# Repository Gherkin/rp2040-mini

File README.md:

# A small MCU board using rp2040

ibom: https://gherkin.github.io/rp2040-mini/

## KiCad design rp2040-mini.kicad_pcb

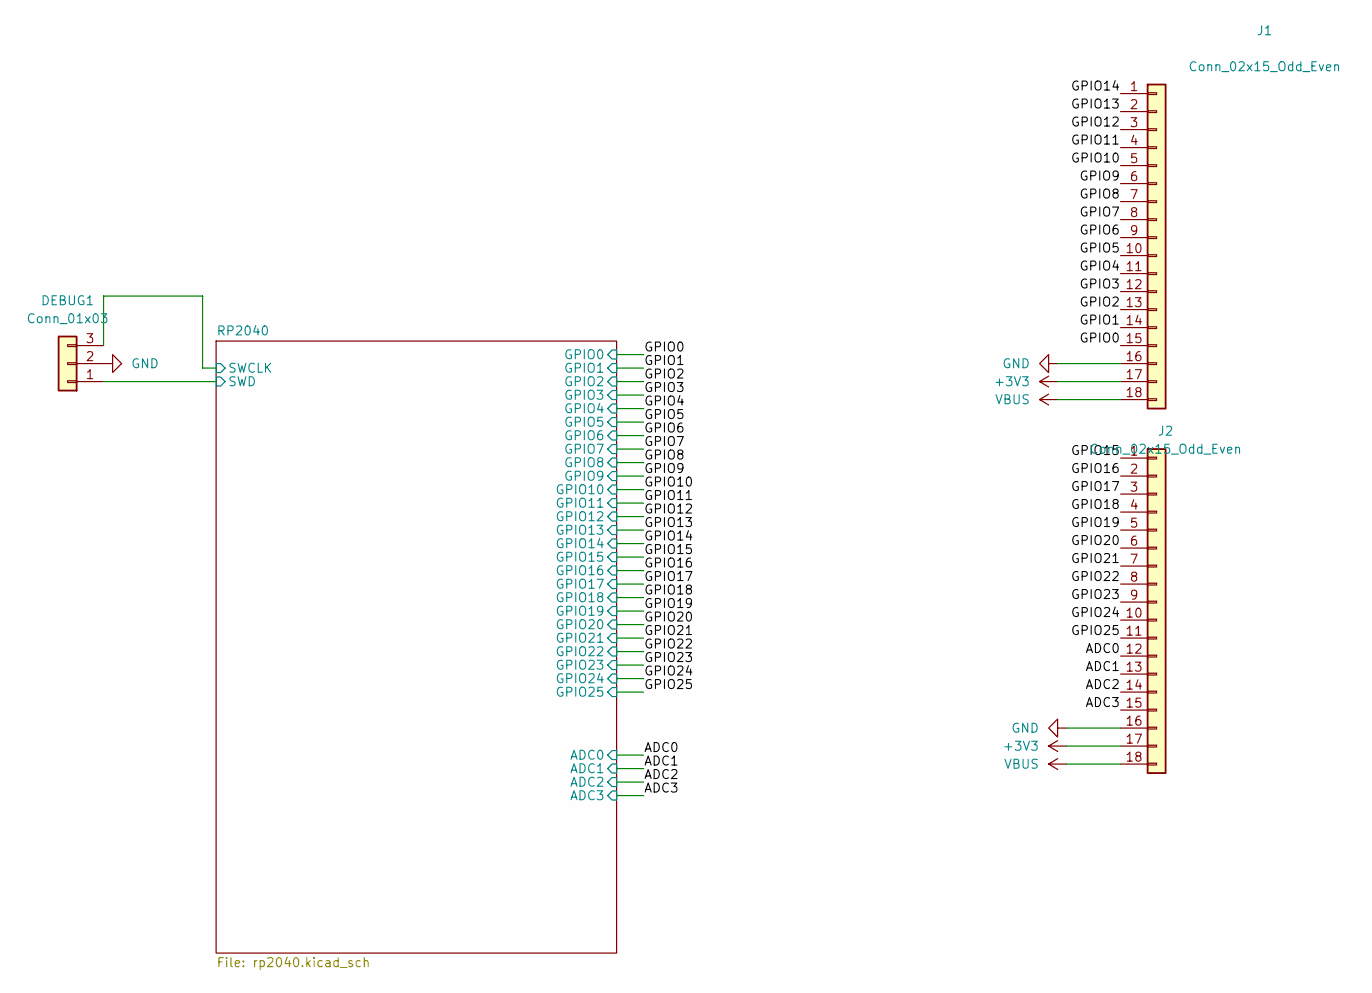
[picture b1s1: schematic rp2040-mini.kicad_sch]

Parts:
DEBUG1: Conn_01x03; PinHeader_1x03_P2.54mm_Vertical
J1, J2: Conn_02x15_Odd_Even; PinSocket_1x18_P2.54mm_Vertical

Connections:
+3V3: J1.17, J2.17; also elsewhere on the board
/ADC0: J2.12; also elsewhere on the board
/ADC1: J2.13; also elsewhere on the board
/ADC2: J2.14; also elsewhere on the board
/ADC3: J2.15; also elsewhere on the board
/GPIO0: J1.15; also elsewhere on the board
/GPIO1: J1.14; also elsewhere on the board
/GPIO2: J1.13; also elsewhere on the board
/GPIO3: J1.12; also elsewhere on the board
/GPIO4: J1.11; also elsewhere on the board
/GPIO5: J1.10; also elsewhere on the board
/GPIO6: J1.9; also elsewhere on the board
/GPIO7: J1.8; also elsewhere on the board
/GPIO8: J1.7; also elsewhere on the board
/GPIO9: J1.6; also elsewhere on the board
/GPIO10: J1.5; also elsewhere on the board
/GPIO11: J1.4; also elsewhere on the board
/GPIO12: J1.3; also elsewhere on the board
/GPIO13: J1.2; also elsewhere on the board
/GPIO14: J1.1; also elsewhere on the board
/GPIO15: J2.1; also elsewhere on the board
/GPIO16: J2.2; also elsewhere on the board
/GPIO17: J2.3; also elsewhere on the board
/GPIO18: J2.4; also elsewhere on the board
/GPIO19: J2.5; also elsewhere on the board
/GPIO20: J2.6; also elsewhere on the board
/GPIO21: J2.7; also elsewhere on the board
/GPIO22: J2.8; also elsewhere on the board
/GPIO23: J2.9; also elsewhere on the board
/GPIO24: J2.10; also elsewhere on the board
/GPIO25: J2.11; also elsewhere on the board
GND: DEBUG1.2, J1.16, J2.16; also elsewhere on the board
VBUS: J1.18, J2.18; also elsewhere on the board

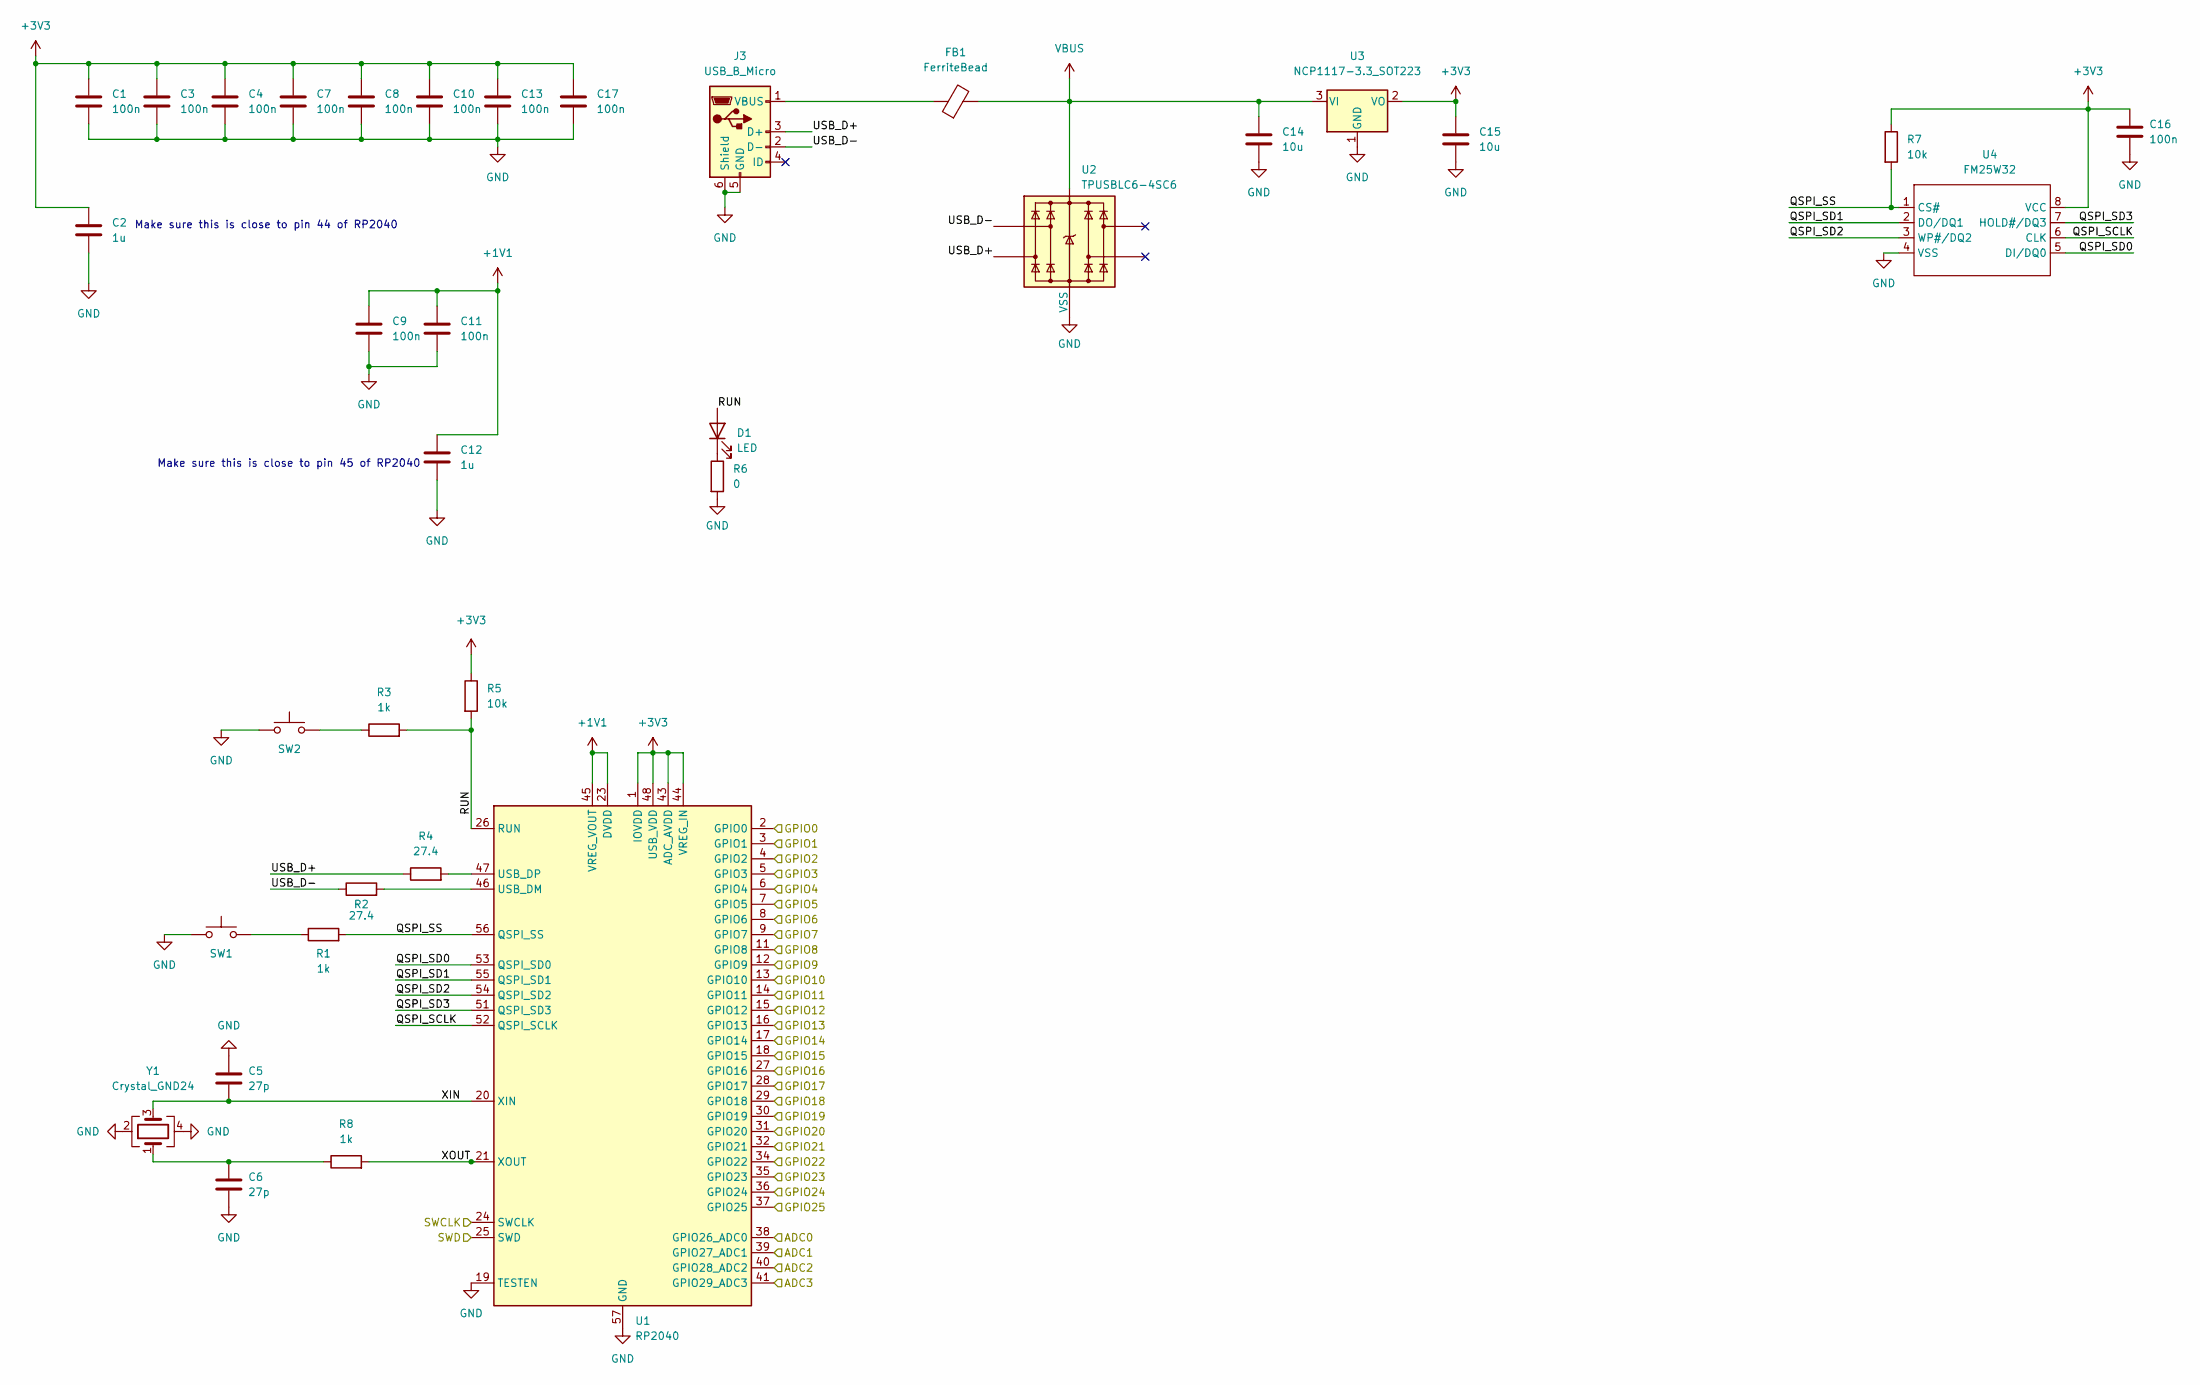
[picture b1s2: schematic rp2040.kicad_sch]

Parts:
C1, C3, C4, C7, C8, C9, C10, C11, C13, C16, C17: 100n; C_0402_1005Metric_Pad0.74x0.62mm_HandSolder; LCSC C60474
C2, C12: 1u; C_0402_1005Metric_Pad0.74x0.62mm_HandSolder; LCSC C59782
C5, C6: 27p; C_0402_1005Metric_Pad0.74x0.62mm_HandSolder; LCSC C107002
C14, C15: 10u; C_0402_1005Metric_Pad0.74x0.62mm_HandSolder; LCSC C85713
D1: LED; LED_0603_1608Metric_Pad1.05x0.95mm_HandSolder; LCSC C965804
FB1: FerriteBead; R_0402_1005Metric_Pad0.72x0.64mm_HandSolder; LCSC C85813
J3: USB_B_Micro; DEALON USB-MR-D-037; LCSC C2927008
R1, R3, R8: 1k; R_0402_1005Metric_Pad0.72x0.64mm_HandSolder; LCSC C114949
R2, R4: 27.4; R_0402_1005Metric_Pad0.72x0.64mm_HandSolder; LCSC C226391
R5, R7: 10k; R_0402_1005Metric_Pad0.72x0.64mm_HandSolder; LCSC C60490
R6: 0; R_0402_1005Metric_Pad0.72x0.64mm_HandSolder; LCSC C60485
SW1, SW2: SW_Push; BZCN TSC003A0826A; LCSC C2888477
U1: RP2040; QFN-56-1EP_7x7mm_P0.4mm_EP3.2x3.2mm; LCSC C2040
U2: TPUSBLC6-4SC6; SOT-23-6_Handsoldering; LCSC C558419
U3: NCP1117-3.3_SOT223; SOT-223-3_TabPin2; LCSC C26537
U4: FM25W32; SOP-8_5.28x5.23mm_P1.27mm; LCSC C609616
Y1: Crystal_GND24; Crystal_SMD_3225-4Pin_3.2x2.5mm; LCSC C9002

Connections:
+1V1: C9.1, C11.1, C12.1, U1.23 (DVDD), U1.45 (VREG_VOUT), U1.50 (DVDD)
+3V3: C1.1, C2.1, C3.1, C4.1, C7.1, C8.1, C10.1, C13.1, C15.1, C16.1, C17.1, R5.1, R7.1, U1.1 (IOVDD), U1.10 (IOVDD), U1.22 (IOVDD), U1.33 (IOVDD), U1.42 (IOVDD), U1.43 (ADC_AVDD), U1.44 (VREG_IN), U1.48 (USB_VDD), U1.49 (IOVDD), U3.2 (VO), U4.8 (VCC); also elsewhere on the board
/ADC0: U1.38 (GPIO26_ADC0); also elsewhere on the board
/ADC1: U1.39 (GPIO27_ADC1); also elsewhere on the board
/ADC2: U1.40 (GPIO28_ADC2); also elsewhere on the board
/ADC3: U1.41 (GPIO29_ADC3); also elsewhere on the board
/GPIO0: U1.2 (GPIO0); also elsewhere on the board
/GPIO1: U1.3 (GPIO1); also elsewhere on the board
/GPIO2: U1.4 (GPIO2); also elsewhere on the board
/GPIO3: U1.5 (GPIO3); also elsewhere on the board
/GPIO4: U1.6 (GPIO4); also elsewhere on the board
/GPIO5: U1.7 (GPIO5); also elsewhere on the board
/GPIO6: U1.8 (GPIO6); also elsewhere on the board
/GPIO7: U1.9 (GPIO7); also elsewhere on the board
/GPIO8: U1.11 (GPIO8); also elsewhere on the board
/GPIO9: U1.12 (GPIO9); also elsewhere on the board
/GPIO10: U1.13 (GPIO10); also elsewhere on the board
/GPIO11: U1.14 (GPIO11); also elsewhere on the board
/GPIO12: U1.15 (GPIO12); also elsewhere on the board
/GPIO13: U1.16 (GPIO13); also elsewhere on the board
/GPIO14: U1.17 (GPIO14); also elsewhere on the board
/GPIO15: U1.18 (GPIO15); also elsewhere on the board
/GPIO16: U1.27 (GPIO16); also elsewhere on the board
/GPIO17: U1.28 (GPIO17); also elsewhere on the board
/GPIO18: U1.29 (GPIO18); also elsewhere on the board
/GPIO19: U1.30 (GPIO19); also elsewhere on the board
/GPIO20: U1.31 (GPIO20); also elsewhere on the board
/GPIO21: U1.32 (GPIO21); also elsewhere on the board
/GPIO22: U1.34 (GPIO22); also elsewhere on the board
/GPIO23: U1.35 (GPIO23); also elsewhere on the board
/GPIO24: U1.36 (GPIO24); also elsewhere on the board
/GPIO25: U1.37 (GPIO25); also elsewhere on the board
/RP2040/QSPI_SCLK: U1.52 (QSPI_SCLK), U4.6 (CLK)
/RP2040/QSPI_SD0: U1.53 (QSPI_SD0), U4.5 (DI/DQ0)
/RP2040/QSPI_SD1: U1.55 (QSPI_SD1), U4.2 (DO/DQ1)
/RP2040/QSPI_SD2: U1.54 (QSPI_SD2), U4.3 (WP#/DQ2)
/RP2040/QSPI_SD3: U1.51 (QSPI_SD3), U4.7 (HOLD#/DQ3)
/RP2040/QSPI_SS: R1.2, R7.2, U1.56 (QSPI_SS), U4.1 (CS#)
/RP2040/RUN: D1.2 (A), R3.2, R5.2, U1.26 (RUN)
/RP2040/SWCLK: U1.24 (SWCLK); also elsewhere on the board
/RP2040/SWD: U1.25 (SWD); also elsewhere on the board
/RP2040/USB_D+: J3.3 (D+), R4.1, U2.1
/RP2040/USB_D-: J3.2 (D-), R2.1, U2.6
/RP2040/XIN: C5.2, U1.20 (XIN), Y1.3
/RP2040/XOUT: R8.2, U1.21 (XOUT)
GND: C1.2, C2.2, C3.2, C4.2, C5.1, C6.2, C7.2, C8.2, C9.2, C10.2, C11.2, C12.2, C13.2, C14.2, C15.2, C16.2, C17.2, J3.5 (GND), J3.6 (Shield), R6.2, SW1.1, SW2.1, U1.19 (TESTEN), U1.57 (GND), U2.2 (VSS), U3.1 (GND), U4.4 (VSS), Y1.2, Y1.4; also elsewhere on the board
unnamed: C6.1, R8.1, Y1.1
unnamed: D1.1 (K), R6.1
unnamed: FB1.1, J3.1 (VBUS)
unnamed: R1.1, SW1.2
unnamed: R2.2, U1.46 (USB_DM)
unnamed: R3.1, SW2.2
unnamed: R4.2, U1.47 (USB_DP)
VBUS: C14.1, FB1.2, U2.5, U3.3 (VI); also elsewhere on the board

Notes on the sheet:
Make sure this is close to pin 45 of RP2040
Make sure this is close to pin 44 of RP2040

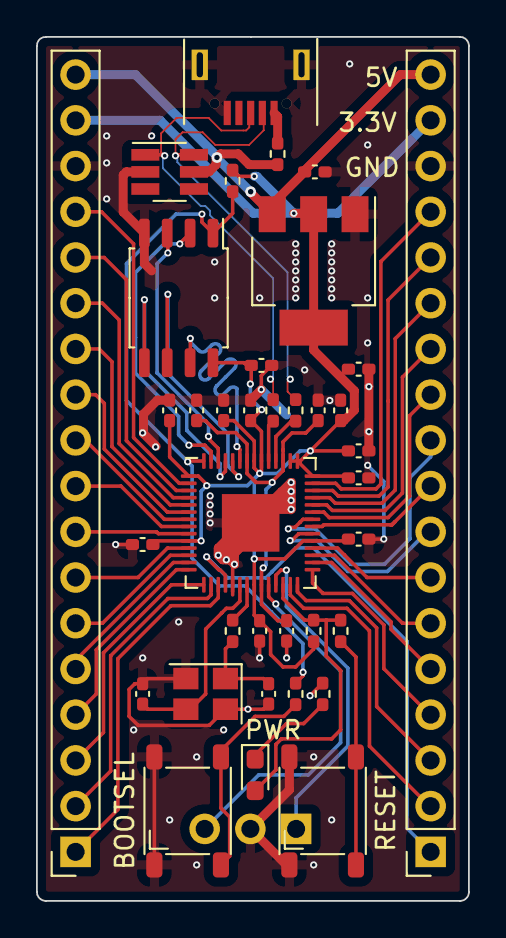
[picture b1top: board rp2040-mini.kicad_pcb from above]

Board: 4 copper layers, 24.0 x 48.0 mm, 38 parts (1 on the bottom side), 54 nets.

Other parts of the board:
DEBUG: Conn_01x03; PinHeader_1x03_P2.54mm_Vertical

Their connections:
/RP2040/SWCLK: DEBUG.3; also elsewhere on the board
/RP2040/SWD: DEBUG.1; also elsewhere on the board
GND: DEBUG.2; also elsewhere on the board

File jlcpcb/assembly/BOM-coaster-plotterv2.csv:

Comment,Designator,Footprint,LCSC
27p,"C5,C6",C_0402_1005Metric_Pad0.74x0.62mm_HandSolder,C107002
1k,"R1,R3,R8",R_0402_1005Metric_Pad0.72x0.64mm_HandSolder,C114949
RP2040,U1,QFN-56-1EP_7x7mm_P0.4mm_EP3.2x3.2mm,C2040
27.4,"R2,R4",R_0402_1005Metric_Pad0.72x0.64mm_HandSolder,C226391
NCP1117-3.3_SOT223,U3,SOT-223-3_TabPin2,C26537
SW_Push,"SW1,SW2",BZCN TSC003A0826A,C2888477
USB_B_Micro,J3,DEALON USB-MR-D-037,C2927008
TPUSBLC6-4SC6,U2,SOT-23-6_Handsoldering,C558419
1u,"C12,C2",C_0402_1005Metric_Pad0.74x0.62mm_HandSolder,C59782
100n,"C1,C10,C11,C13,C16,C17,C3,C4,C7,C8,C9",C_0402_1005Metric_Pad0.74x0.62mm_HandSolder,C60474
R,R6,R_0402_1005Metric_Pad0.72x0.64mm_HandSolder,C60485
10k,"R5,R7",R_0402_1005Metric_Pad0.72x0.64mm_HandSolder,C60490
FM25W32,U4,SOP-8_5.28x5.23mm_P1.27mm,C609616
10u,"C14,C15",C_0402_1005Metric_Pad0.74x0.62mm_HandSolder,C85713
FerriteBead,FB1,R_0402_1005Metric_Pad0.72x0.64mm_HandSolder,C85813
Crystal_GND24,Y1,Crystal_SMD_3225-4Pin_3.2x2.5mm,C9002
LED,D1,LED_0603_1608Metric_Pad1.05x0.95mm_HandSolder,C965804
Conn_02x15_Odd_Even,J1,PinSocket_1x18_P2.54mm_Vertical,
Conn_02x15_Odd_Even,J2,PinSocket_1x18_P2.54mm_Vertical,

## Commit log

2022-06-27 initial v1.0 commit
2022-06-27 added 3d image and README
2022-10-29 moved the rp2040 core schematic to its own subrepo
2022-10-29 forgot some shit in last commit
